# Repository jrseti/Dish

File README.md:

# Dish Repository

This repository contains hardware and firmware work for refurbishing a legacy
3-meter satellite dish into a modern, networked robotic system.

The design is split into two PCB projects that work together over CAN:

## Projects

### 1. `controller/` - RCM Dish Controller Board

The main motion-control and compute board for the dish.

- STM32-based two-axis motion controller
- On-board Raspberry Pi Compute Module 4 carrier
- Power, I/O, communications, and safety/control interfaces
- KiCad hardware design plus associated embedded/software assets

See: [controller/README.md](controller/README.md)

### 2. `can_hub/` - CAN Bus Hub

A simple CAN distribution hub that also routes 24 V power to CAN_V+ pins.

See: [can_hub/README.md](can_hub/README.md)

## Repository Layout

- `controller/`: Main controller electronics, docs, and software
- `can_hub/`: CAN power/distribution hub hardware

## Purpose

Together, these boards provide the control and field-bus backbone for the dish:

- `controller/` runs motion control and local host integration
- `can_hub/` provides CAN/power fan-out for connected nodes

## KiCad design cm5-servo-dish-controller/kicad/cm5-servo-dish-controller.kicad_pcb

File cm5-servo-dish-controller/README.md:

# CM5 Servo Dish Controller

A radio astronomy dish controller: a carrier board for a Raspberry Pi Compute
Module 5 (CM5) with an STM32G474 that drives the dish's servo motors over CANopen.

The board is derived from
[roboclaw-cm4-dc-dish-controller](https://github.com/jrseti/roboclaw-cm4-dc-dish-controller).
The RoboClaw motor controller is replaced by an STM32G474RET6, which is the CANopen
master for external servo drives (such as the DSY-400C) and runs the position and
velocity loop. The board runs from 5 V DC, supplied by an external Mean Well
DDR-60L-5 converter that isolates it from the 48 V battery. The CAN bus is isolated
and has two jacks, one to the drives and one to the nodes on the dish, which it
powers with 24 V from a second external converter. The board uses a CM5 in place
of the CM4, and has two USB 3.0 ports.

**Schematic:** [kicad/cm5-servo-dish-controller.pdf](kicad/cm5-servo-dish-controller.pdf)

**Design description and open items:** [DESIGN.md](DESIGN.md)

## Status

The schematic is a complete first pass and passes KiCad's electrical rules check.
The PCB layout, the STM32 firmware and the CM5 software have not been started.

## Repository layout

This project is one folder of the Dish repository:

```
Dish/
├── parts/                        # git submodule: KiCad symbol, footprint and 3D-model library
└── cm5-servo-dish-controller/    # this project: README.md, DESIGN.md
    └── kicad/                    # KiCad 10 project: schematic and PCB
```

## Cloning

The KiCad project finds its symbols, footprints and 3D models in the `parts/`
submodule at the root of the Dish repository (`${KIPRJMOD}/../../parts`). Clone with:

```sh
git clone --recurse-submodules <repository-url>
```

If you have already cloned the repository, run `git submodule update --init`.

KiCad finds the 3D models and datasheets through two path variables. Set them in
**Preferences → Configure Paths**:

| Variable | Value |
|---|---|
| `MYPARTS` | `<clone>/parts` |
| `MYPARTS_DATASHEETS` | `<clone>/parts/datasheets` |

## Hardware

Open `kicad/cm5-servo-dish-controller.kicad_pro` with KiCad 10.

## License

This project is licensed under the MIT License. See [LICENSE](LICENSE) for details.

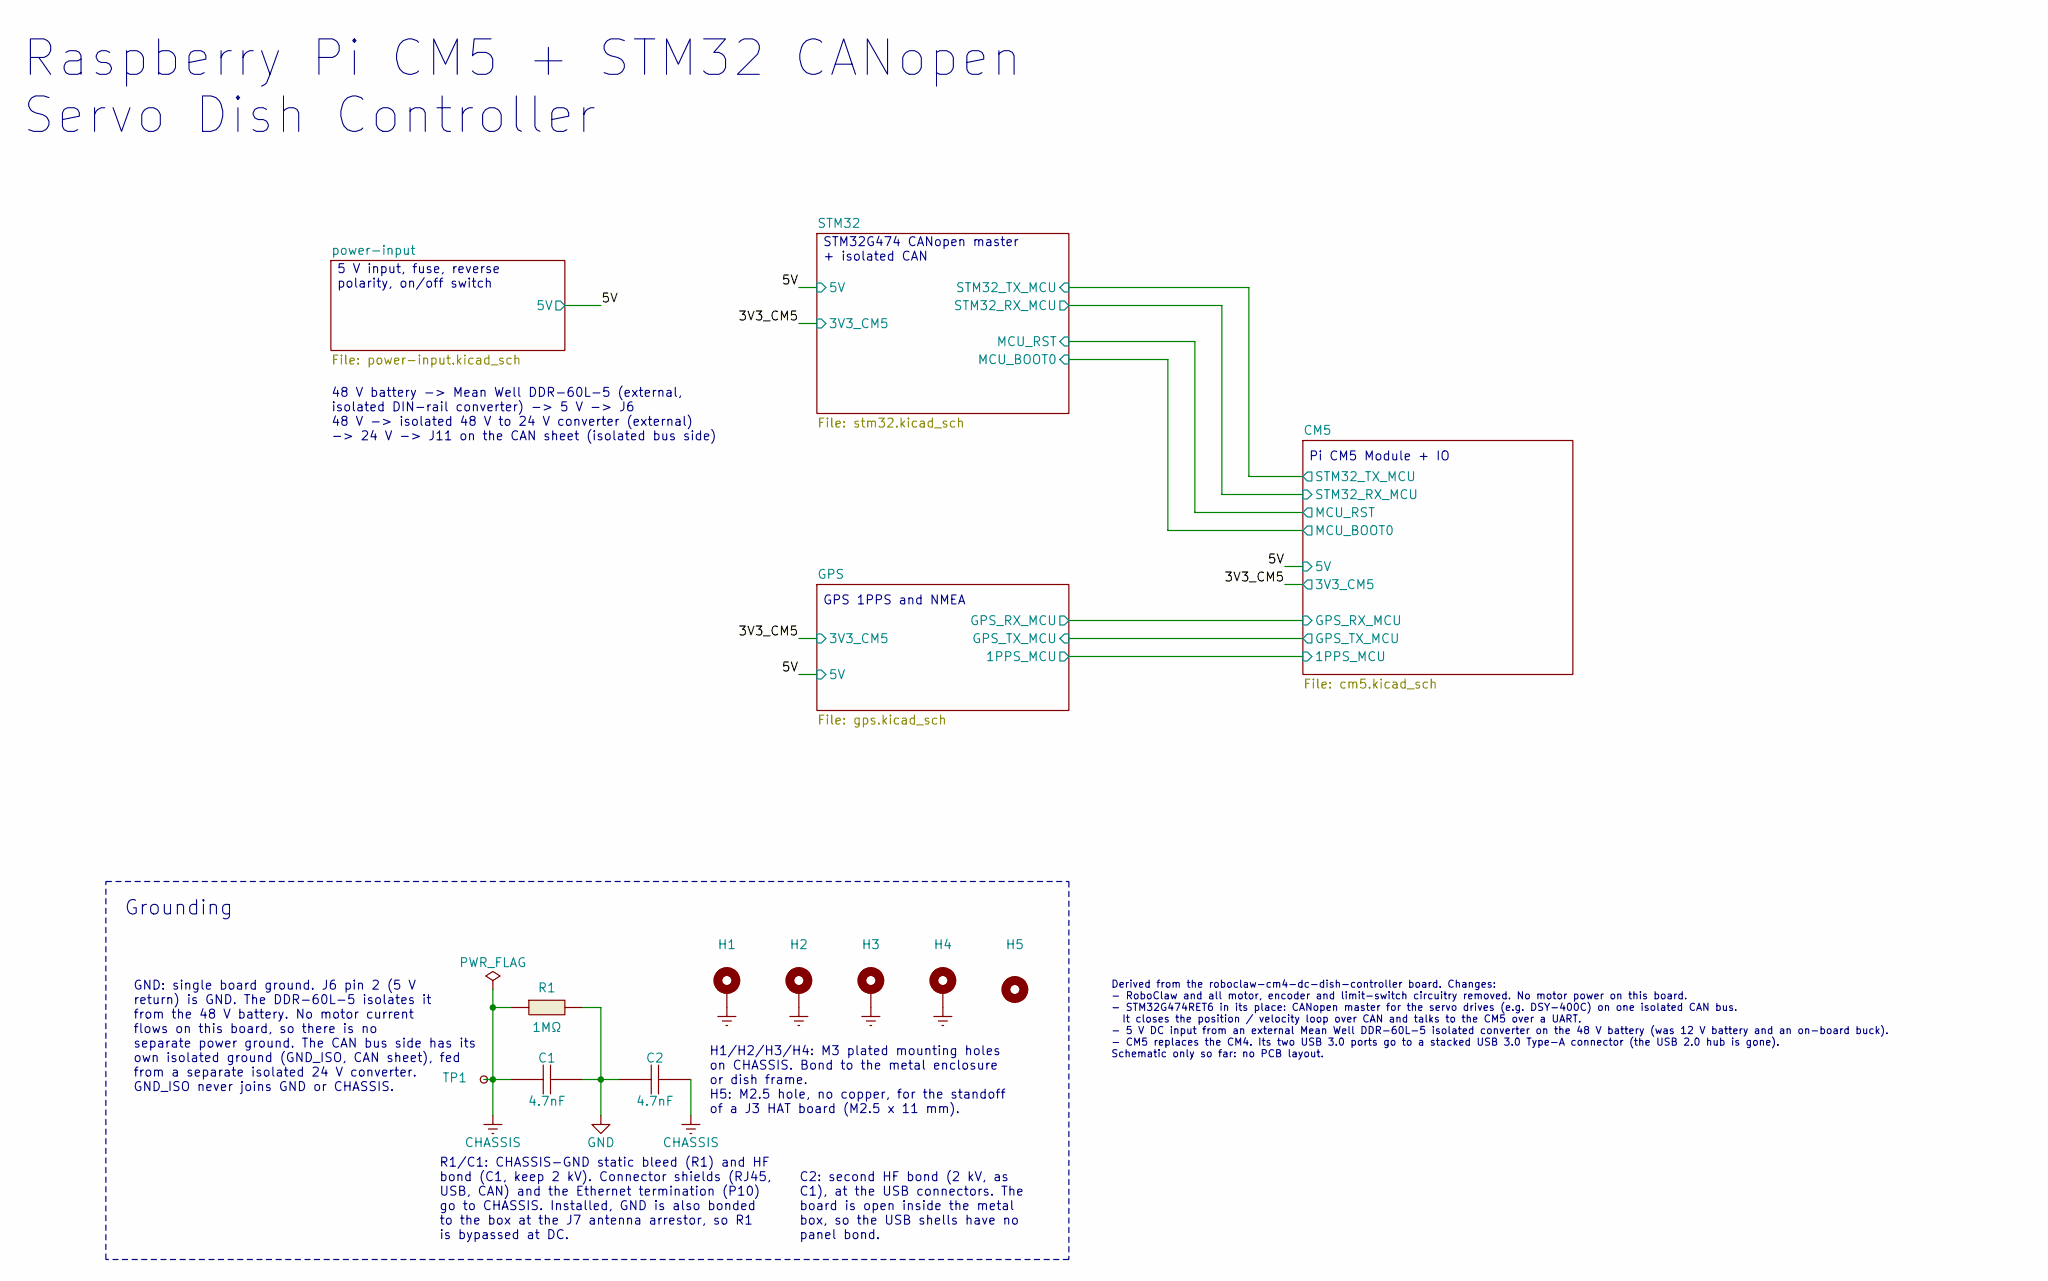
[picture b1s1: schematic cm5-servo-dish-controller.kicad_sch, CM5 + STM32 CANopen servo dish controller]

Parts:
C1, C2: 4.7nF; CAPC3216X180N; Tolerance ±10%; Voltage Rating 2kV; MPN 1206B472K202NT; LCSC Part C41017
H1, H2, H3, H4: M3; MountingHole_3.2mm_M3_Pad_Via
H5: M2.5; MountingHole_2.7mm_M2.5
R1: 1MΩ; RESC3216X70N; Tolerance ±1%; Voltage Rating 200V; MPN 1206W4F1004T5E; LCSC Part C17927
TP1: TestPoint_Small; TestPoint_Pad_D0.8mm

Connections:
CHASSIS: C1.1, C2.2, H1.1 (1_1), H2.1 (1_1), H3.1 (1_1), H4.1 (1_1), R1.1, TP1.1 (1_1); also elsewhere on the board
GND: C1.2, C2.1, R1.2; also elsewhere on the board

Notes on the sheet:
GND: single board ground. J6 pin 2 (5 V return) is GND. The DDR-60L-5 isolates it from the 48 V battery. No motor current flows on this board, so there is no separate power ground. The CAN bus side has its own isolated ground (GND_ISO, CAN sheet), fed from a separate isolated 24 V converter. GND_IS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
STM32G474 CANopen master + isolated CAN
H1/H2/H3/H4: M3 plated mounting holes on CHASSIS. Bond to the metal enclosure or dish frame. H5: M2.5 hole, no copper, for the standoff of a J3 HAT board (M2.5 x 11 mm).
Raspberry Pi CM5 + STM32 CANopen Servo Dish Controller
Pi CM5 Module + IO
C2: second HF bond (2 kV, as C1), at the USB connectors. The board is open inside the metal box, so the USB shells have no panel bond.
R1/C1: CHASSIS-GND static bleed (R1) and HF bond (C1, keep 2 kV). Connector shields (RJ45, USB, CAN) and the Ethernet termination (P10) go to CHASSIS. Installed, GND is also bonded to the box at the J7 antenna arrestor, so R1 is bypassed at DC.
48 V battery -> Mean Well DDR-60L-5 (external, isolated DIN-rail converter) -> 5 V -> J6 48 V -> isolated 48 V to 24 V converter (external) -> 24 V -> J11 on the CAN sheet (isolated bus side)
Derived from the roboclaw-cm4-dc-dish-controller board. Changes: - RoboClaw and all motor, encoder and limit-switch circuitry removed. No motor power on this board. - STM32G474RET6 in its place: CANopen master for the servo drives (e.g. DSY-400C) on one isolated CAN bus. It closes the position / ve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
GPS 1PPS and NMEA
5 V input, fuse, reverse polarity, on/off switch
Grounding

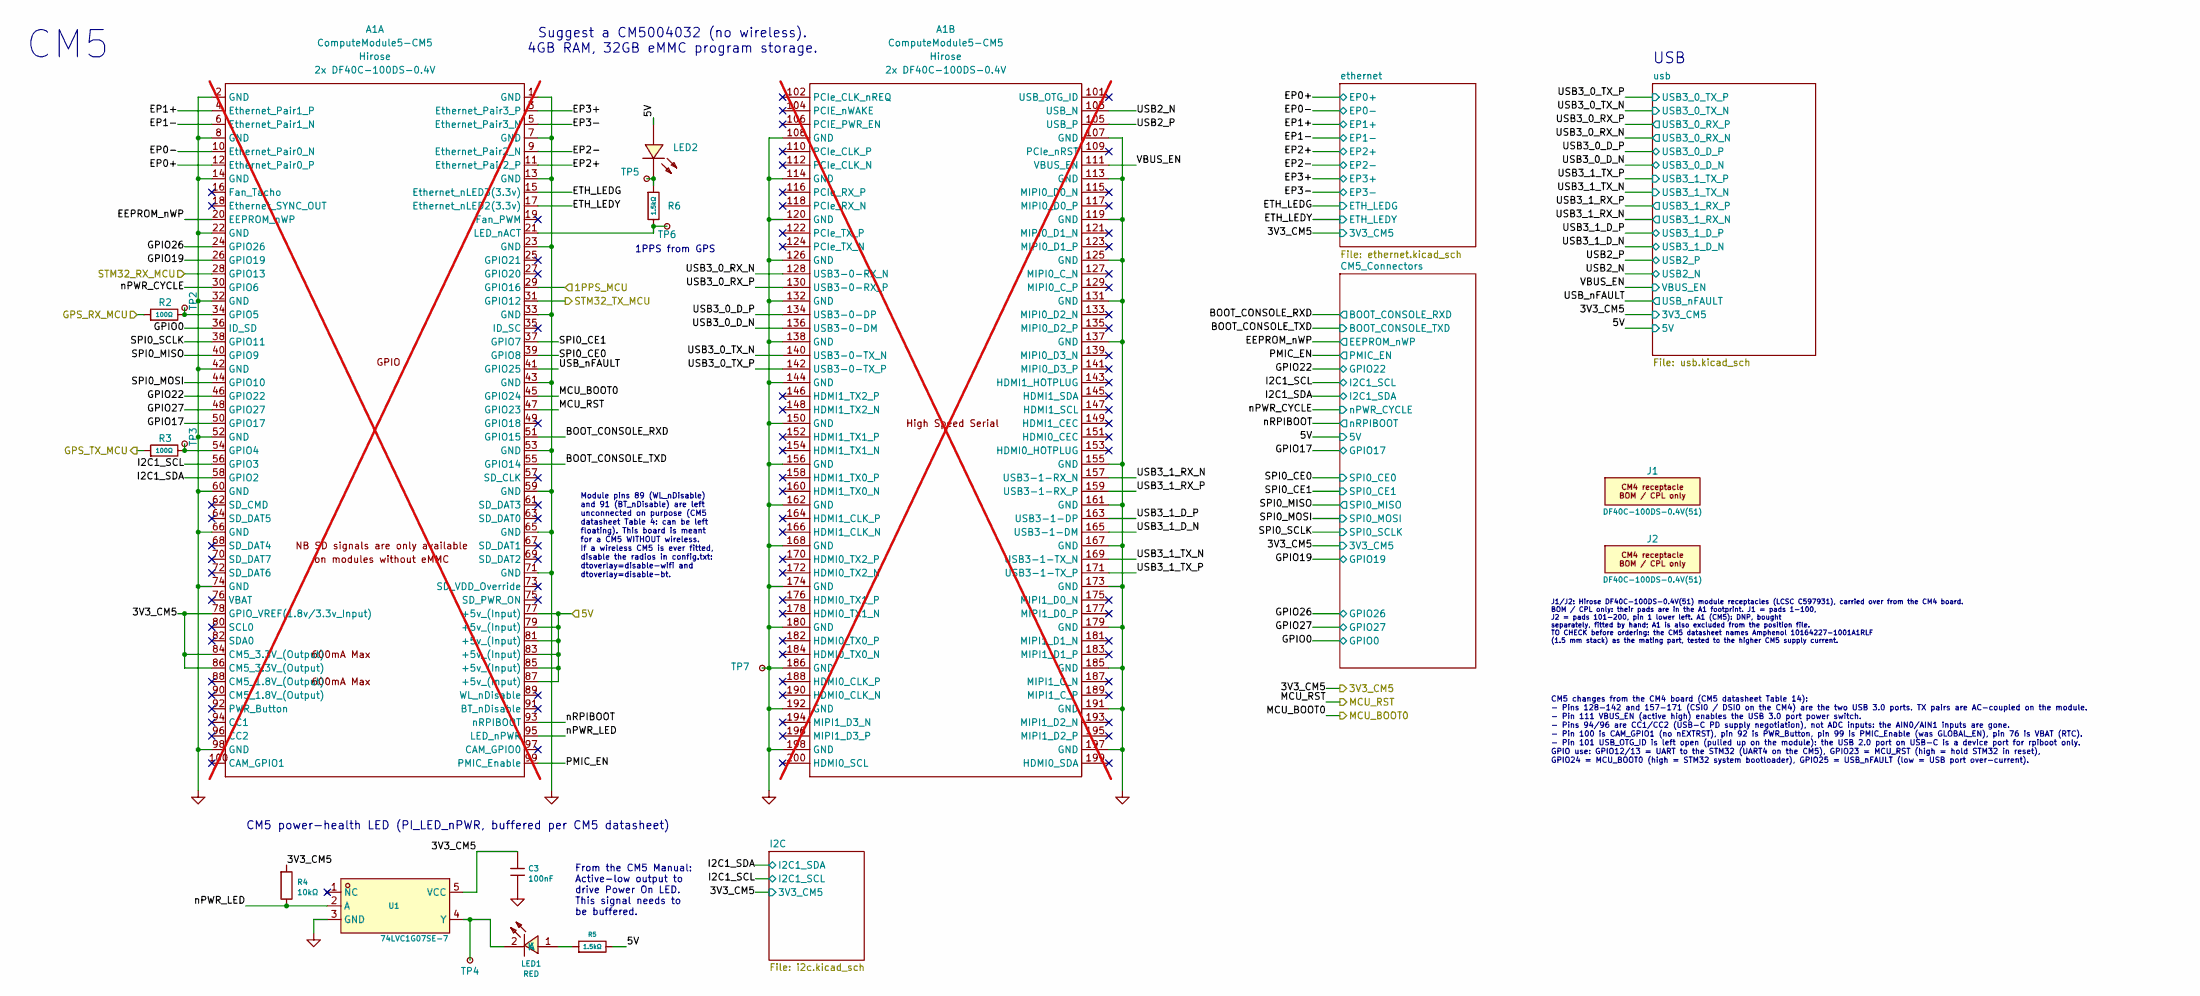
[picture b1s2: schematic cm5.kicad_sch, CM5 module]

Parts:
A1: ComputeModule5-CM5; RaspberryPi_CM4_CM5; MPN SC1559; not fitted
C3: 100nF; CAPC1005X55N; Tolerance ±10%; Voltage Rating 16V; MPN CL05B104KO5NNNC; LCSC Part C1525
J1, J2: DF40C-100DS-0.4V(51); Hirose_DF40C-100DS-0.4V_BOM-ONLY; MPN DF40C-100DS-0.4V(51); LCSC Part C597931
LED1: RED; LEDC2012X110N; MPN KT-0805R; LCSC Part C2295
LED2: GREEN; LEDC2012X110N; MPN KT-0805G; LCSC Part C2297
R2, R3: 100Ω; RESC1005X40N; Tolerance ±1%; Voltage Rating 50V; MPN 0402WGF1000TCE; LCSC Part C25076
R4: 10kΩ; RESC1005X40N; Tolerance ±1%; Voltage Rating 50V; MPN 0402WGF1002TCE; LCSC Part C25744
R5, R6: 1.5kΩ; RESC1005X40N; Tolerance ±1%; Voltage Rating 50V; MPN 0402WGF1501TCE; LCSC Part C25867
TP2, TP3, TP4, TP5, TP6, TP7: TestPoint_Small; TestPoint_Pad_D0.8mm
U1: 74LVC1G07SE-7; SOT65P210X110-5N; MPN 74LVC1G07SE-7; LCSC Part C67531

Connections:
/3V3_CM5: A1.78 (GPIO_VREF(1.8v/3.3v_Input)), A1.84 (CM5_3.3V_(Output)), A1.86 (CM5_3.3V_(Output)), C3.1, R4.1, U1.5 (VCC); also elsewhere on the board
/5V: A1.77 (+5v_(Input)), A1.79 (+5v_(Input)), A1.81 (+5v_(Input)), A1.83 (+5v_(Input)), A1.85 (+5v_(Input)), A1.87 (+5v_(Input)), LED2.1 (A), R5.2; also elsewhere on the board
/CM5/1PPS_MCU: A1.29 (GPIO16); also elsewhere on the board
/CM5/BOOT_CONSOLE_RXD: A1.51 (GPIO15); also elsewhere on the board
/CM5/BOOT_CONSOLE_TXD: A1.55 (GPIO14); also elsewhere on the board
/CM5/EEPROM_nWP: A1.20 (EEPROM_nWP); also elsewhere on the board
/CM5/EP0+: A1.12 (Ethernet_Pair0_P); also elsewhere on the board
/CM5/EP0-: A1.10 (Ethernet_Pair0_N); also elsewhere on the board
/CM5/EP1+: A1.4 (Ethernet_Pair1_P); also elsewhere on the board
/CM5/EP1-: A1.6 (Ethernet_Pair1_N); also elsewhere on the board
/CM5/EP2+: A1.11 (Ethernet_Pair2_P); also elsewhere on the board
/CM5/EP2-: A1.9 (Ethernet_Pair2_N); also elsewhere on the board
/CM5/EP3+: A1.3 (Ethernet_Pair3_P); also elsewhere on the board
/CM5/EP3-: A1.5 (Ethernet_Pair3_N); also elsewhere on the board
/CM5/ETH_LEDG: A1.15 (Ethernet_nLED3(3.3v)); also elsewhere on the board
/CM5/ETH_LEDY: A1.17 (Ethernet_nLED2(3.3v)); also elsewhere on the board
/CM5/GPIO0: A1.36 (ID_SD); also elsewhere on the board
/CM5/GPIO17: A1.50 (GPIO17); also elsewhere on the board
/CM5/GPIO19: A1.26 (GPIO19); also elsewhere on the board
/CM5/GPIO22: A1.46 (GPIO22); also elsewhere on the board
/CM5/GPIO26: A1.24 (GPIO26); also elsewhere on the board
/CM5/GPIO27: A1.48 (GPIO27); also elsewhere on the board
/CM5/GPS_RX_MCU: R2.1; also elsewhere on the board
/CM5/GPS_TX_MCU: R3.1; also elsewhere on the board
/CM5/I2C1_SCL: A1.56 (GPIO3); also elsewhere on the board
/CM5/I2C1_SDA: A1.58 (GPIO2); also elsewhere on the board
/CM5/MCU_BOOT0: A1.45 (GPIO24); also elsewhere on the board
/CM5/MCU_RST: A1.47 (GPIO23); also elsewhere on the board
/CM5/PMIC_EN: A1.99 (PMIC_Enable); also elsewhere on the board
/CM5/SPI0_CE0: A1.39 (GPIO8); also elsewhere on the board
/CM5/SPI0_CE1: A1.37 (GPIO7); also elsewhere on the board
/CM5/SPI0_MISO: A1.40 (GPIO9); also elsewhere on the board
/CM5/SPI0_MOSI: A1.44 (GPIO10); also elsewhere on the board
/CM5/SPI0_SCLK: A1.38 (GPIO11); also elsewhere on the board
/CM5/STM32_RX_MCU: A1.28 (GPIO13); also elsewhere on the board
/CM5/STM32_TX_MCU: A1.31 (GPIO12); also elsewhere on the board
/CM5/USB2_N: A1.103 (USB_N); also elsewhere on the board
/CM5/USB2_P: A1.105 (USB_P); also elsewhere on the board
/CM5/USB3_0_D_N: A1.136 (USB3-0-DM); also elsewhere on the board
/CM5/USB3_0_D_P: A1.134 (USB3-0-DP); also elsewhere on the board
/CM5/USB3_0_RX_N: A1.128 (USB3-0-RX_N); also elsewhere on the board
/CM5/USB3_0_RX_P: A1.130 (USB3-0-RX_P); also elsewhere on the board
/CM5/USB3_0_TX_N: A1.140 (USB3-0-TX_N); also elsewhere on the board
/CM5/USB3_0_TX_P: A1.142 (USB3-0-TX_P); also elsewhere on the board
/CM5/USB3_1_D_N: A1.165 (USB3-1-DM); also elsewhere on the board
/CM5/USB3_1_D_P: A1.163 (USB3-1-DP); also elsewhere on the board
/CM5/USB3_1_RX_N: A1.157 (USB3-1-RX_N); also elsewhere on the board
/CM5/USB3_1_RX_P: A1.159 (USB3-1-RX_P); also elsewhere on the board
/CM5/USB3_1_TX_N: A1.169 (USB3-1-TX_N); also elsewhere on the board
/CM5/USB3_1_TX_P: A1.171 (USB3-1-TX_P); also elsewhere on the board
/CM5/USB_nFAULT: A1.41 (GPIO25); also elsewhere on the board
/CM5/VBUS_EN: A1.111 (VBUS_EN); also elsewhere on the board
/CM5/nPWR_CYCLE: A1.30 (GPIO6); also elsewhere on the board
/CM5/nPWR_LED: A1.95 (LED_nPWR), R4.2, U1.2 (A)
/CM5/nRPIBOOT: A1.93 (nRPIBOOT); also elsewhere on the board
GND: A1.1 (GND), A1.2 (GND), A1.7 (GND), A1.8 (GND), A1.13 (GND), A1.14 (GND), A1.22 (GND), A1.23 (GND), A1.32 (GND), A1.33 (GND), A1.42 (GND), A1.43 (GND), A1.52 (GND), A1.53 (GND), A1.59 (GND), A1.60 (GND), A1.65 (GND), A1.66 (GND), A1.71 (GND), A1.74 (GND), A1.98 (GND), A1.107 (GND), A1.108 (GND), A1.113 (GND), A1.114 (GND), A1.119 (GND), A1.120 (GND), A1.125 (GND), A1.126 (GND), A1.131 (GND), A1.132 (GND), A1.137 (GND), A1.138 (GND), A1.144 (GND), A1.150 (GND), A1.155 (GND), A1.156 (GND), A1.161 (GND), A1.162 (GND), A1.167 (GND), A1.168 (GND), A1.173 (GND), A1.174 (GND), A1.179 (GND), A1.180 (GND), A1.185 (GND), A1.186 (GND), A1.191 (GND), A1.192 (GND), A1.197 (GND), A1.198 (GND), C3.2, TP7.1 (1_1), U1.3 (GND); also elsewhere on the board
unnamed: A1.54 (GPIO4), R3.2, TP3.1 (1_1)
unnamed: A1.34 (GPIO5), R2.2, TP2.1 (1_1)
unnamed: A1.21 (LED_nACT), R6.2, TP6.1 (1_1)
unnamed: LED1.1 (A), R5.1
unnamed: LED1.2 (K), TP4.1 (1_1), U1.4 (Y)
unnamed: LED2.2 (K), R6.1, TP5.1 (1_1)

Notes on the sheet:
CM5 power-health LED (PI_LED_nPWR, buffered per CM5 datasheet)
J1/J2: Hirose DF40C-100DS-0.4V(51) module receptacles (LCSC C597931), carried over from the CM4 board. BOM / CPL only: their pads are in the A1 footprint. J1 = pads 1-100, J2 = pads 101-200, pin 1 lower left. A1 (CM5): DNP, bought separately, fitted by hand; A1 is also excluded from the position fi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
USB
Module pins 89 (WL_nDisable) and 91 (BT_nDisable) are left unconnected on purpose (CM5 datasheet Table 4: can be left floating). This board is meant for a CM5 WITHOUT wireless. If a wireless CM5 is ever fitted, disable the radios in config.txt: dtoverlay=disable-wifi and dtoverlay=disable-bt.
CM5
Suggest a CM5004032 (no wireless). 4GB RAM, 32GB eMMC program storage.
From the CM5 Manual: Active-low output to drive Power On LED. This signal needs to be buffered.
1PPS from GPS
CM5 changes from the CM4 board (CM5 datasheet Table 14): - Pins 128-142 and 157-171 (CSI0 / DSI0 on the CM4) are the two USB 3.0 ports. TX pairs are AC-coupled on the module. - Pin 111 VBUS_EN (active high) enables the USB 3.0 port power switch. - Pins 94/96 are CC1/CC2 (USB-C PD supply negotiation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

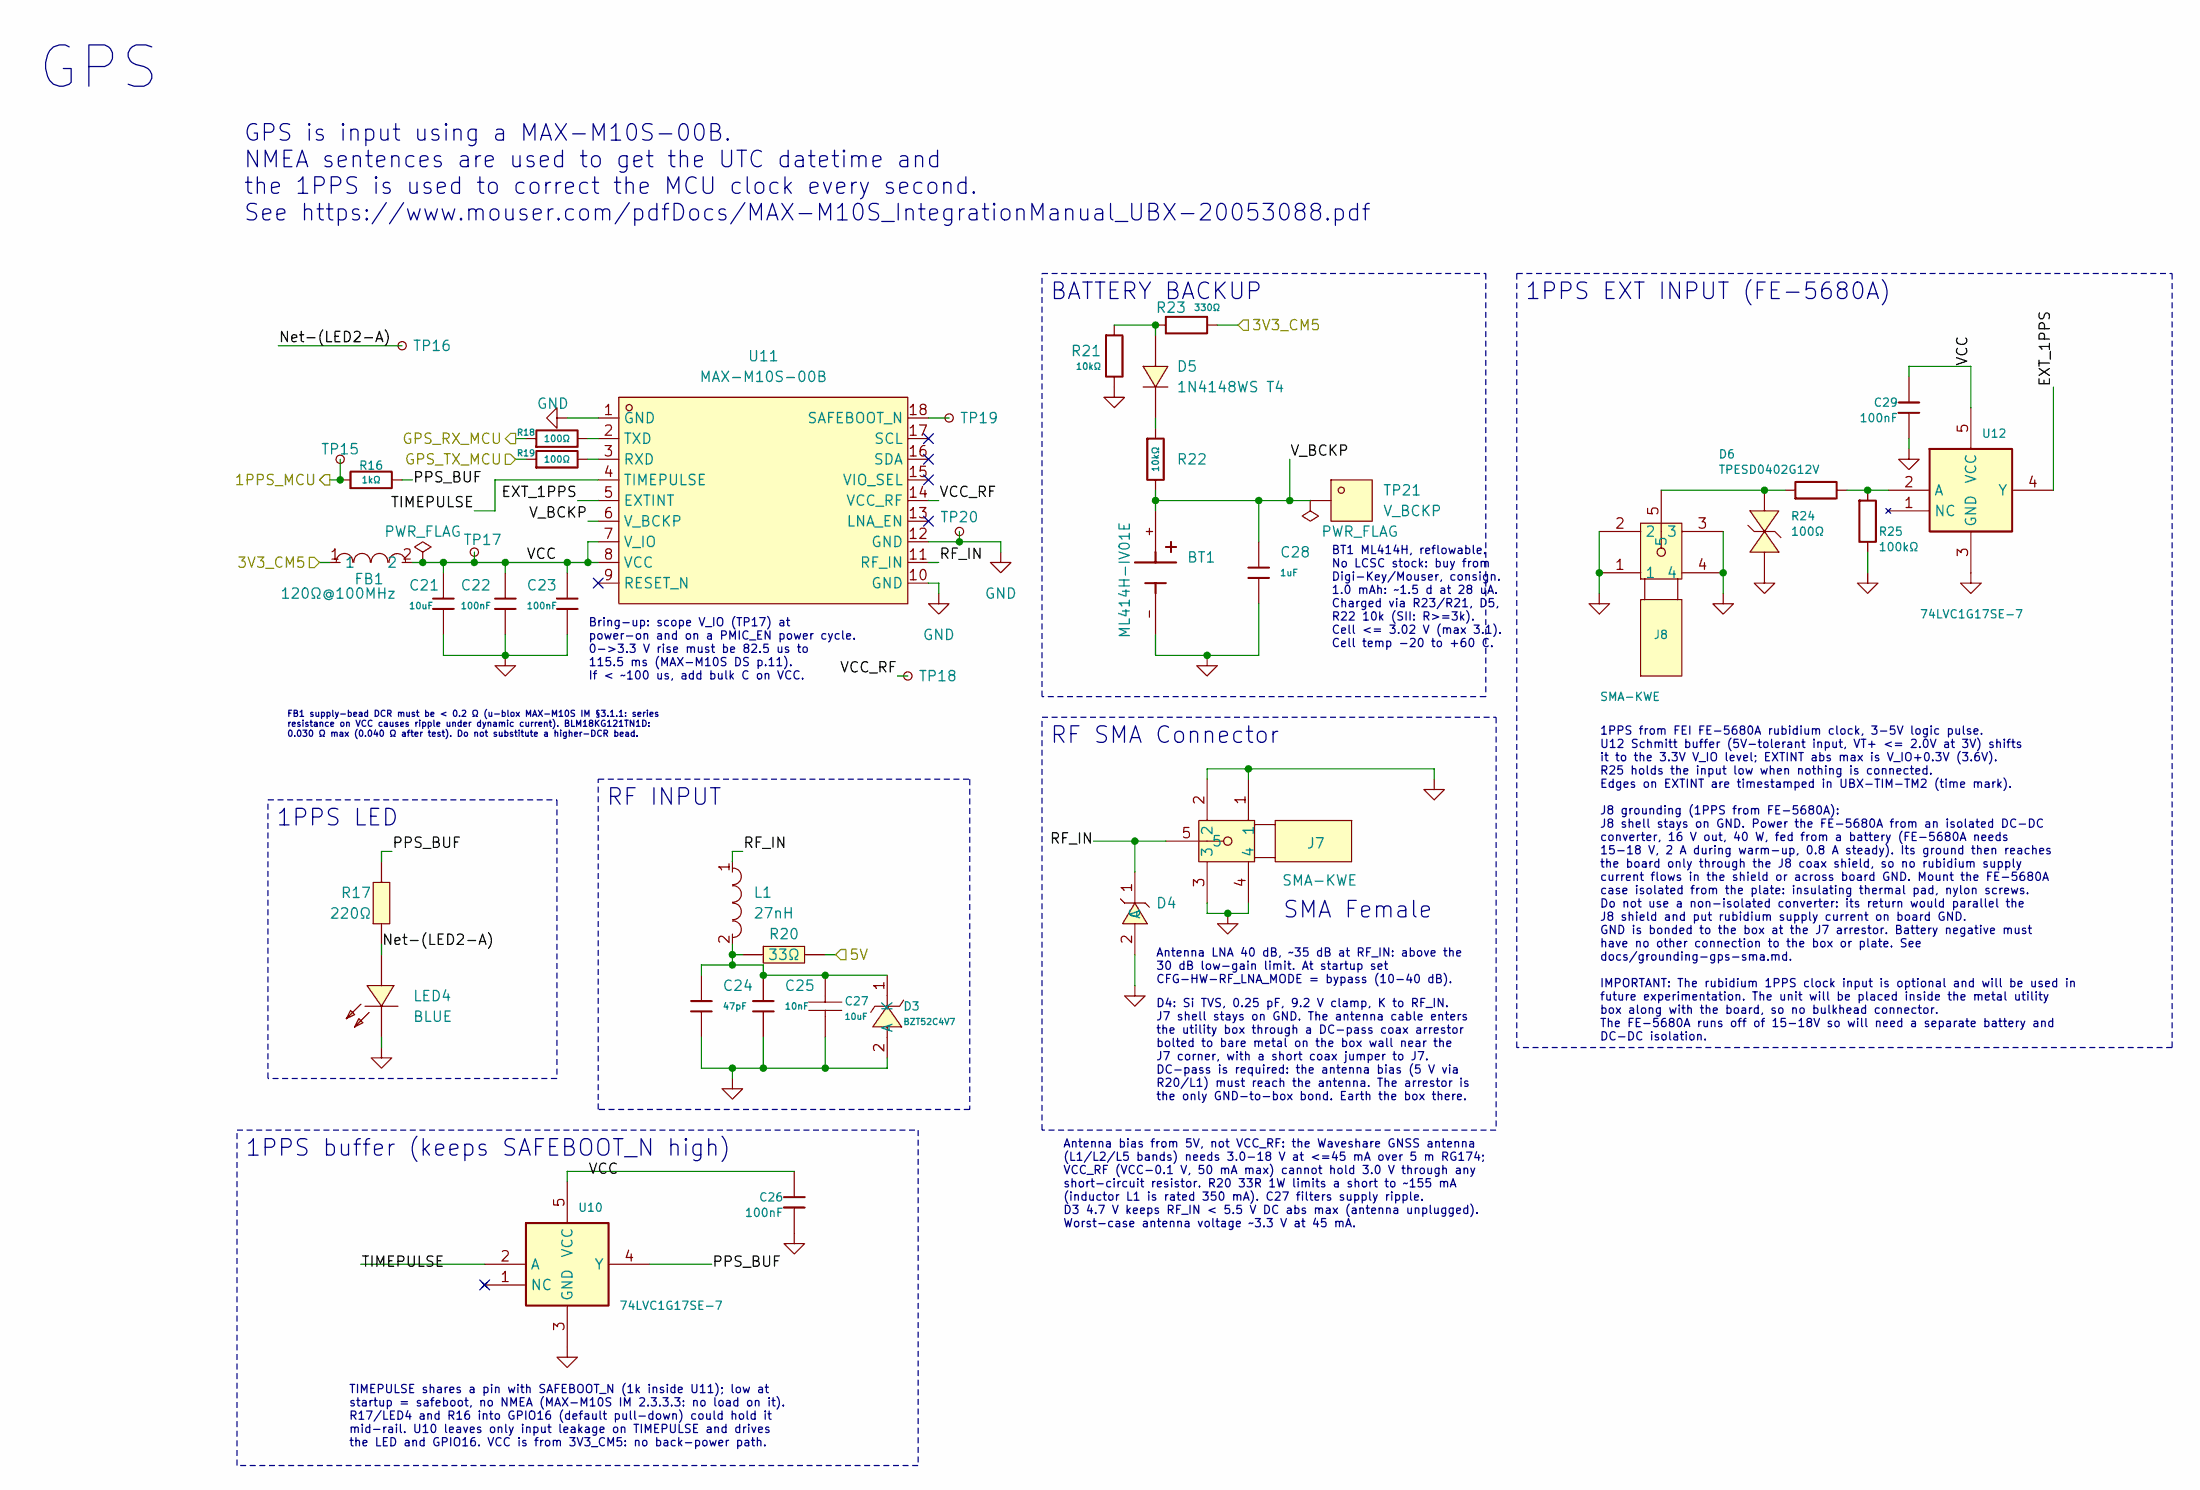
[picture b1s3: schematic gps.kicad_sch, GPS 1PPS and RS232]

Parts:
BT1: ML414H-IV01E; Seiko_ML414H-IV01E; PARTREV E
C21: 10uF; CAPC1608X95N; Tolerance ±20%; Voltage Rating 25V; MPN CL10A106MA8NRNC; LCSC Part C96446
C22, C23, C26, C29: 100nF; CAPC1608X95N; Tolerance ±10%; Voltage Rating 50V; MPN CC0603KRX7R9BB104; LCSC Part C14663
C24: 47pF; CAPC1608X95N; Tolerance ±5%; Voltage Rating 50V; MPN CL10C470JB8NNNC; LCSC Part C1671
C25: 10nF; CAPC1608X95N; Tolerance ±10%; Voltage Rating 50V; MPN 0603B103K500NT; LCSC Part C57112
C27: 10uF; CAPC2012X145N; Tolerance ±10%; Voltage Rating 10V; MPN CL21B106KPQNNNE; LCSC Part C32635
C28: 1uF; CAPC1608X95N; Tolerance ±10%; Voltage Rating 50V; MPN CL10A105KB8NNNC; LCSC Part C15849
D3: BZT52C4V7; SOD3716X135N; MPN BZT52C4V7; LCSC Part C19077400
D4: SESD0402X1UN-0020-090; DIOC1006X40N; MPN SESD0402X1UN-0020-090; LCSC Part C1973340
D5: 1N4148WS T4; SOD2513X110N; MPN 1N4148WS; LCSC Part C2128
D6: TPESD0402G12V; DIOC1005X55N; MPN TPESD0402G12V; LCSC Part C558617
FB1: 120Ω@100MHz; INDC1608X95N; Tolerance ±25%; Current Rating 3A; MPN BLM18KG121TN1D; LCSC Part C85831
J7, J8: SMA-KWE; LX_SMA-KWE; MPN SMA-KWE; LCSC Part C7498154
L1: 27nH; INDC1005X55N; Tolerance ±5%; Current Rating 350mA; MPN LQG15HS27NJ02D; LCSC Part C12669
LED4: BLUE; LEDC2012X110N; MPN KT-0805B; LCSC Part C2293
R16: 1kΩ; RESC1005X40N; Tolerance ±1%; Voltage Rating 50V; MPN 0402WGF1001TCE; LCSC Part C11702
R17: 220Ω; RESC1005X40N; Tolerance ±1%; Voltage Rating 50V; MPN 0402WGF2200TCE; LCSC Part C25091
R18, R19, R24: 100Ω; RESC1005X40N; Tolerance ±1%; Voltage Rating 50V; MPN 0402WGF1000TCE; LCSC Part C25076
R20: 33Ω; RESC6332X70N; Tolerance ±1%; Voltage Rating 200V; MPN 25121WF330JT4E; LCSC Part C53728
R21, R22: 10kΩ; RESC1608X55N; Tolerance ±1%; Voltage Rating 75V; MPN 0603WAF1002T5E; LCSC Part C25804
R23: 330Ω; RESC1608X55N; Tolerance ±1%; Voltage Rating 75V; MPN 0603WAF3300T5E; LCSC Part C23138
R25: 100kΩ; RESC1608X55N; Tolerance ±1%; Voltage Rating 75V; MPN 0603WAF1003T5E; LCSC Part C25803
TP15, TP16, TP17, TP18, TP19, TP20: TestPoint_Small; TestPoint_Pad_D0.8mm
TP21: V_BCKP; Ronghe_RH-5016; MPN RH-5016; LCSC Part C5199799
U10, U12: 74LVC1G17SE-7; SOT65P210X110-5N; MPN 74LVC1G17SE-7; LCSC Part C212314
U11: MAX-M10S-00B; u-blox_MAX-M10S; MPN MAX-M10S-00B; LCSC Part C4153167

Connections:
/3V3_CM5: FB1.1, R23.2; also elsewhere on the board
/5V: R20.2; also elsewhere on the board
/CM5/1PPS_MCU: R16.1, TP15.1 (1_1); also elsewhere on the board
/CM5/GPS_RX_MCU: R18.1; also elsewhere on the board
/CM5/GPS_TX_MCU: R19.1; also elsewhere on the board
/GPS/EXT_1PPS: U11.5 (EXTINT), U12.4 (Y)
/GPS/Net-(LED2-A): LED4.1 (A), R17.1, TP16.1 (1_1)
/GPS/PPS_BUF: R16.2, R17.2, U10.4 (Y)
/GPS/RF_IN: D4.1 (C), J7.5, L1.1, U11.11 (RF_IN)
/GPS/TIMEPULSE: U10.2 (A), U11.4 (TIMEPULSE)
/GPS/VCC: C21.1, C22.1, C23.1, C26.1, C29.1, FB1.2, TP17.1 (1_1), U10.5 (VCC), U11.7 (V_IO), U11.8 (VCC), U12.5 (VCC)
/GPS/VCC_RF: TP18.1 (1_1), U11.14 (VCC_RF)
/GPS/V_BCKP: BT1.+, C28.1, R22.2, TP21.1 (1_1), U11.6 (V_BCKP)
GND: BT1.-, C21.2, C22.2, C23.2, C24.2, C25.2, C26.2, C27.1, C28.2, C29.2, D3.2 (A), D4.2 (A), D6.1 (K), J7.1, J7.2, J7.3, J7.4, J8.1, J8.2, J8.3, J8.4, LED4.2 (K), R21.2, R25.2, TP20.1 (1_1), U10.3 (GND), U11.1 (GND), U11.10 (GND), U11.12 (GND), U12.3 (GND); also elsewhere on the board
unnamed: C24.1, C25.1, C27.2, D3.1 (K), L1.2, R20.1
unnamed: D5.2 (A), R21.1, R23.1
unnamed: D5.1 (K), R22.1
unnamed: D6.2 (A), J8.5, R24.1
unnamed: R19.2, U11.3 (RXD)
unnamed: TP19.1 (1_1), U11.18 (SAFEBOOT_N)
unnamed: R18.2, U11.2 (TXD)
unnamed: R24.2, R25.1, U12.2 (A)

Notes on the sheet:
GPS
Bring-up: scope V_IO (TP17) at power-on and on a PMIC_EN power cycle. 0->3.3 V rise must be 82.5 us to 115.5 ms (MAX-M10S DS p.11). If < ~100 us, add bulk C on VCC.
1PPS from FEI FE-5680A rubidium clock, 3-5V logic pulse. U12 Schmitt buffer (5V-tolerant input, VT+ <= 2.0V at 3V) shifts it to the 3.3V V_IO level; EXTINT abs max is V_IO+0.3V (3.6V). R25 holds the input low when nothing is connected. Edges on EXTINT are timestamped in UBX-TIM-TM2 (time mark). J8 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
Antenna bias from 5V, not VCC_RF: the Waveshare GNSS antenna (L1/L2/L5 bands) needs 3.0-18 V at <=45 mA over 5 m RG174; VCC_RF (VCC-0.1 V, 50 mA max) cannot hold 3.0 V through any short-circuit resistor. R20 33R 1W limits a short to ~155 mA (inductor L1 is rated 350 mA). C27 filters supply ripple. 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
FB1 supply-bead DCR must be < 0.2 Ω (u-blox MAX-M10S IM §3.1.1: series resistance on VCC causes ripple under dynamic current). BLM18KG121TN1D: 0.030 Ω max (0.040 Ω after test). Do not substitute a higher-DCR bead.
D4: Si TVS, 0.25 pF, 9.2 V clamp, K to RF_IN. J7 shell stays on GND. The antenna cable enters the utility box through a DC-pass coax arrestor bolted to bare metal on the box wall near the J7 corner, with a short coax jumper to J7. DC-pass is required: the antenna bias (5 V via R20/L1) must reach th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
GPS is input using a MAX-M10S-00B. NMEA sentences are used to get the UTC datetime and the 1PPS is used to correct the MCU clock every second. See https://www.mouser.com/pdfDocs/MAX-M10S_IntegrationManual_UBX-20053088.pdf
SMA Female
BT1 ML414H, reflowable. No LCSC stock: buy from Digi-Key/Mouser, consign. 1.0 mAh: ~1.5 d at 28 uA. Charged via R23/R21, D5, R22 10k (SII: R>=3k). Cell <= 3.02 V (max 3.1). Cell temp -20 to +60 C.
TIMEPULSE shares a pin with SAFEBOOT_N (1k inside U11); low at startup = safeboot, no NMEA (MAX-M10S IM 2.3.3.3: no load on it). R17/LED4 and R16 into GPIO16 (default pull-down) could hold it mid-rail. U10 leaves only input leakage on TIMEPULSE and drives the LED and GPIO16. VCC is from 3V3_CM5: no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
Antenna LNA 40 dB, ~35 dB at RF_IN: above the 30 dB low-gain limit. At startup set CFG-HW-RF_LNA_MODE = bypass (10-40 dB).
RF SMA Connector
1PPS EXT INPUT (FE-5680A)
1PPS buffer (keeps SAFEBOOT_N high)
1PPS LED
RF INPUT
BATTERY BACKUP
